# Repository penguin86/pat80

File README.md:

# Pat80

Pat80 Home Computer is an attempt to develop the simplest possible Zilog Z80 based computer in 2021.

## Hardware
Instead of being another single board computer, Pat80 focuses on modularity:
- The Core board contains Z80 CPU, 32k ram, 32k rom, memory and I/O decoding logic
- The Backplane is a stupid I/O bus board with no active components, 1 socket for the Core board and 8 sockets for I/O boards
- Each I/O board must implement tri-state and go to high impedance according to its EN pin to avoid bus contention
- The Power Supply module contains a 7805-based linear power supply capable of delivering 1A @5v for the core and I/O boards

Here is a picture of the early stages of development:

### I/O Boards

#### Parallel terminal interface
A parallel terminal based on Arduino is used for development purposes and will be replaced by an UART card.

#### Keyboard controller
Pat80 features a blue-switches mechanical matrix keyboard, seen by the system as a memory area in I/O space. The keyboard doesn't use interrupts and is polled by the OS.

#### Video controller
The monochrome 368x248 pixels video output is software-generated by an ATMega 1284 MCU. The timings are generated by the MCU's 16 bit internal timer and the vertical sync time is used to update the framebuffer.

## Software
The OS is a simple Memory Monitor. It can show memory content in hex and ascii with the typical hex editor tabular view.
Programs can be loaded from the keyboard, writing Z80 opcodes and data in hex. The program can be executed from any ram position and the Memory Monitor can be brought to screen in any moment issuing an INT signal (the Z80 INT pin should be connected to a button with pull-up resistor).
There is an experimental and unfinished quick load function using a python terminal to load a binary file directly to memory and execute it.

## Emulator
The pat80 memory monitor (the os) can be run in a z80 emulator. This repository contains an emulator as submodule, already set up to run the os.
To try it, head to `pat80-computer/software/z80-assembly/os/Makefile` and run `make run` to build the rom from assembly and start the emulator. You will see some windows showing the emulated computer's memory and register status and the pat80 memory monitor prompt.

## Status
The project is heavily work in progress.

### Working
- Core board
- Sound board
- Arduino parallel terminal with its own Python companion script (or any UART terminal)

The only fully working configuration as now is the Core board with two devices hooked to its I/O bus: the Arduino Parallel Terminal (see `pat80-io-devices/parallel-terminal` and `pat80-computer/software/z80-assembly/os/drivers/arduino_terminal.asm`) and the SN76489 sound chip (see `pat80-computer/software/z80-assembly/os/drivers/hd44780.asm`)

### Partially working
The keyboard is only partially tested, as it's not completed.

The composite video card is partially working, but has some nasty bugs on text cursor positioning and the graphics mode is not yet implemented (the only way to output graphics ATM is to place the bitmap in the MCU flash and load it to VRAM manually).

For the moment, better to stick with the Arduino Parallel Terminal.

### Not working
All the rest

## License
All the project is under GPL v3 license

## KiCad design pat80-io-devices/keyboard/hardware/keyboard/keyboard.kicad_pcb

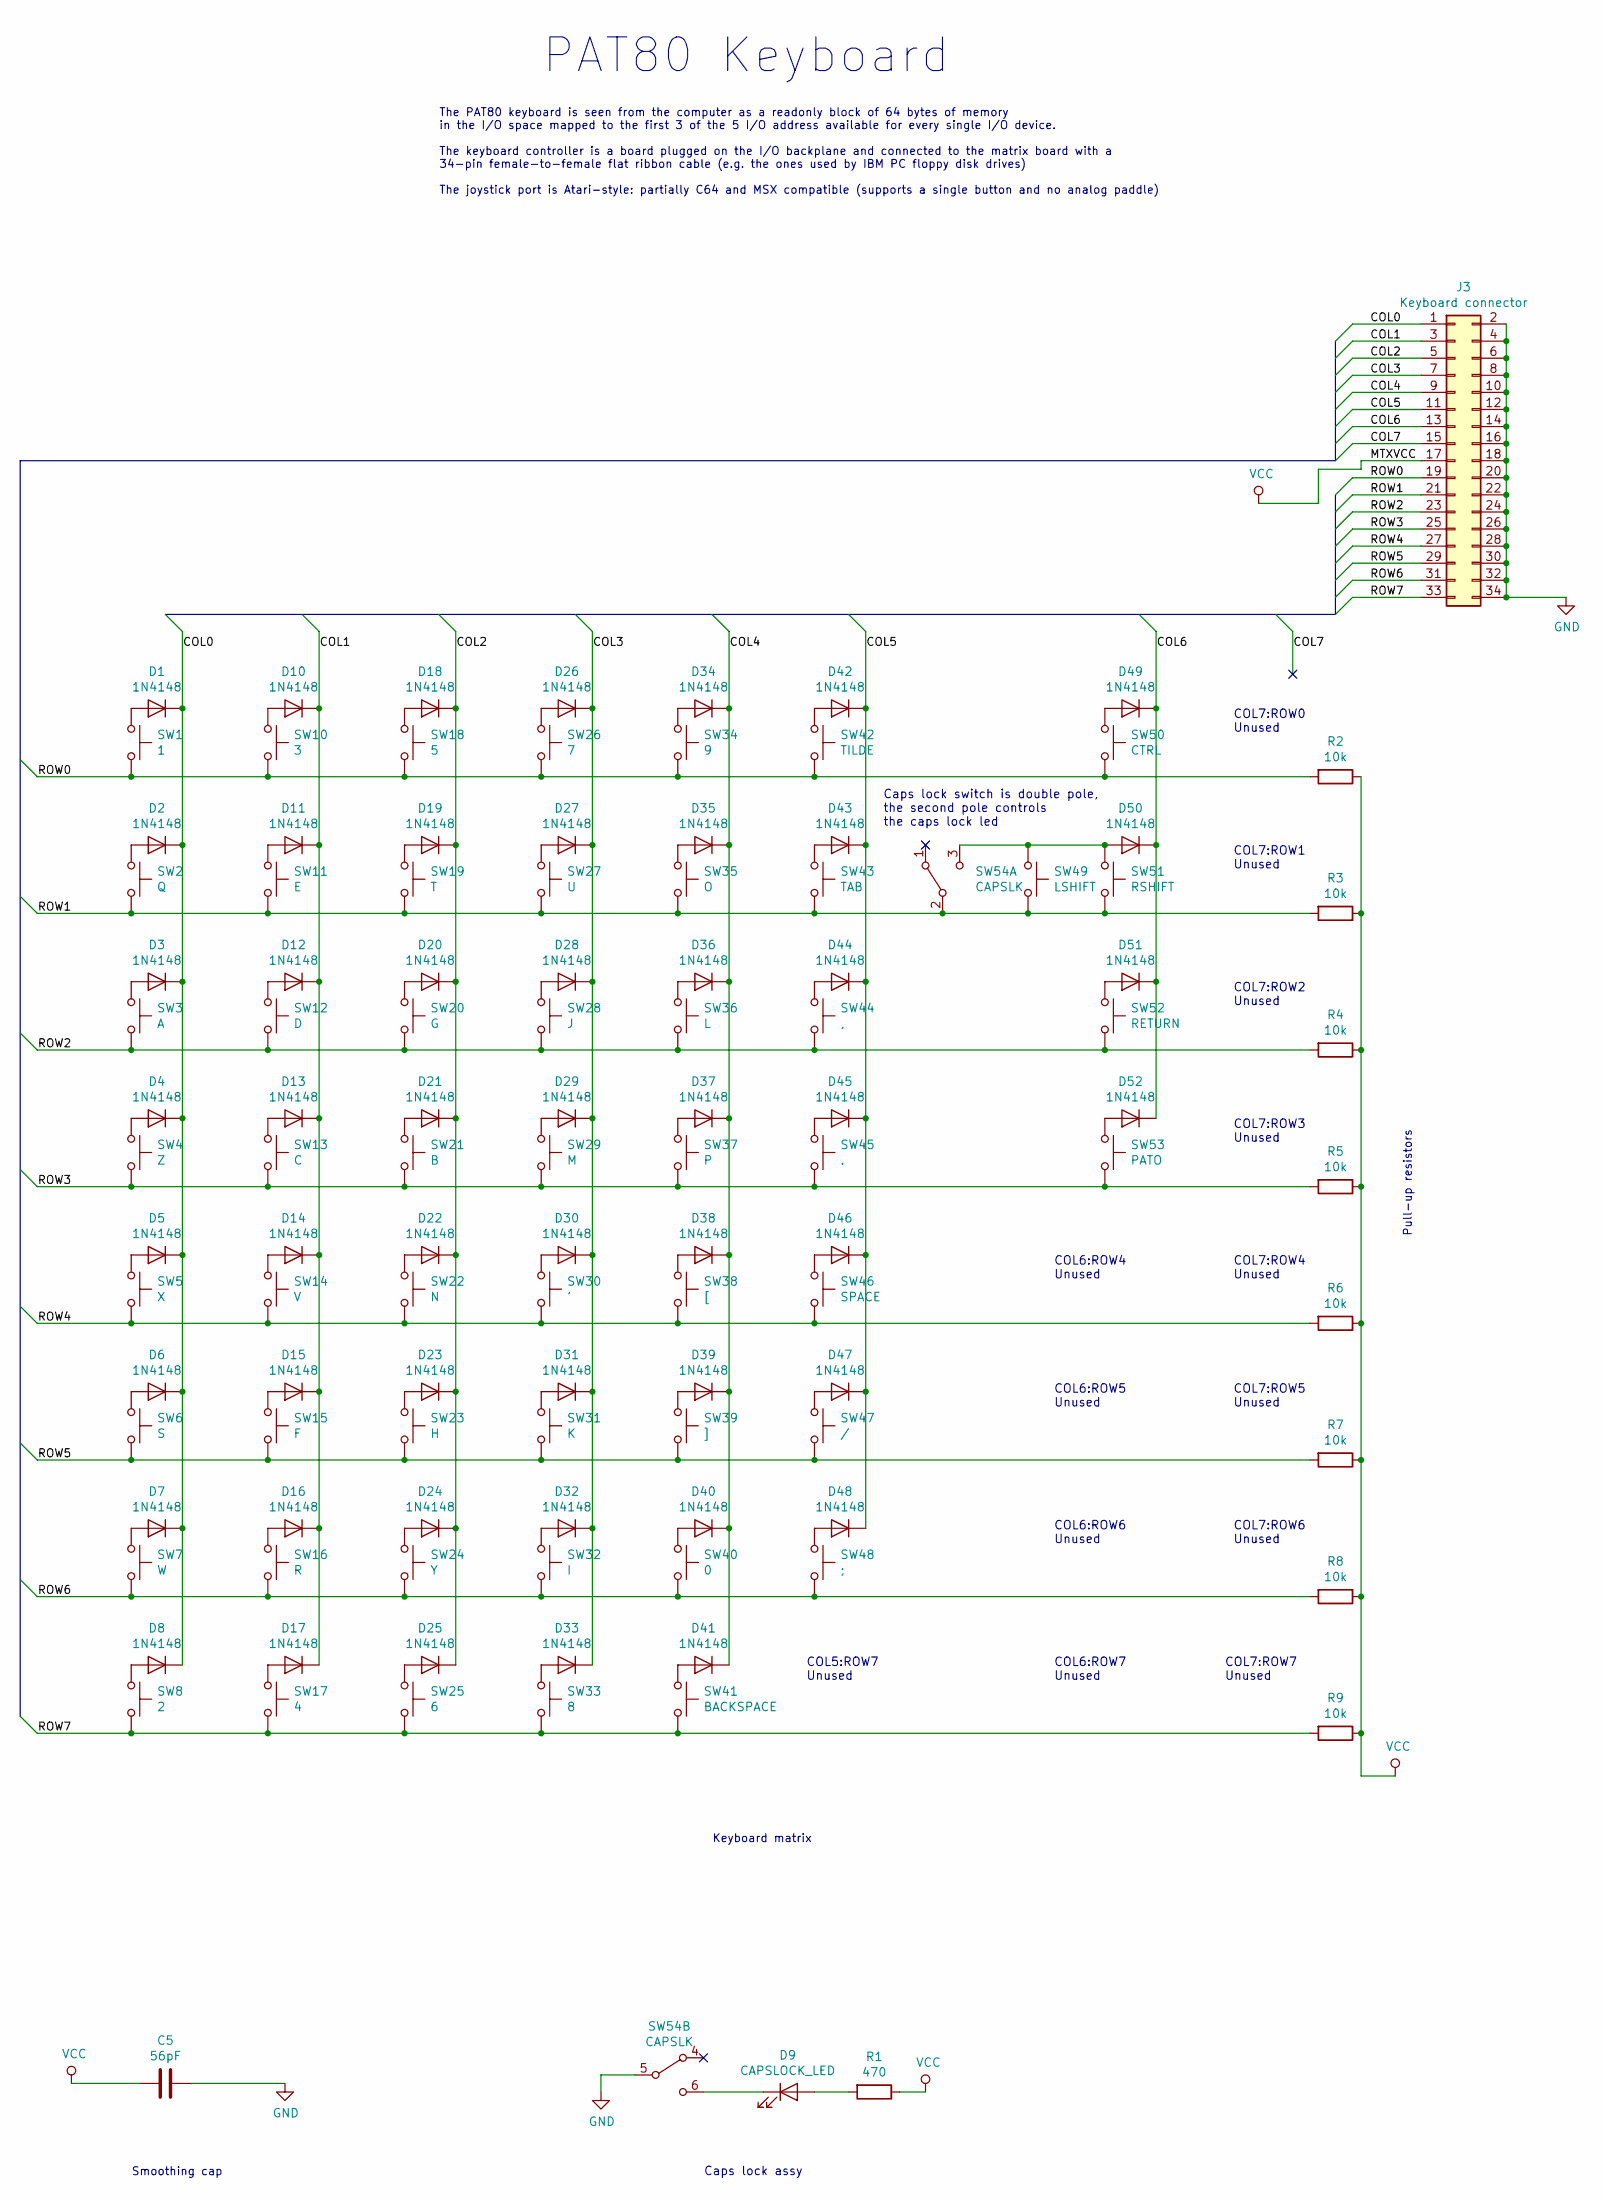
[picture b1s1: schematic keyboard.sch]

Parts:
C5: 56pF; CP_Radial_Tantal_D6.0mm_P5.00mm
D1, D2, D3, D4, D5, D6, D7, D8, D10, D11, D12, D13, D14, D15, D16, D17, D18, D19, D20, D21, D22, D23, D24, D25, D26, D27, D28, D29, D30, D31, D32, D33, D34, D35, D36, D37, D38, D39, D40, D41, D42, D43, D44, D45, D46, D47, D48, D49, D50, D51, D52: 1N4148; D_DO-41_SOD81_P7.62mm_Horizontal
D9: CAPSLOCK_LED; LED_D5.0mm
J3: Keyboard connector; PinHeader_2x17_P2.54mm_Vertical
R1: 470; R_Axial_DIN0207_L6.3mm_D2.5mm_P7.62mm_Horizontal
R2, R3, R4, R5, R6, R7, R8, R9: 10k; R_Axial_DIN0207_L6.3mm_D2.5mm_P7.62mm_Horizontal
SW1: 1; SW_Cherry_MX1A_1.00u_PCB
SW2: Q; SW_Cherry_MX1A_1.00u_PCB
SW3: A; SW_Cherry_MX1A_1.00u_PCB
SW4: Z; SW_Cherry_MX1A_1.00u_PCB
SW5: X; SW_Cherry_MX1A_1.00u_PCB
SW6: S; SW_Cherry_MX1A_1.00u_PCB
SW7: W; SW_Cherry_MX1A_1.00u_PCB
SW8: 2; SW_Cherry_MX1A_1.00u_PCB
SW10: 3; SW_Cherry_MX1A_1.00u_PCB
SW11: E; SW_Cherry_MX1A_1.00u_PCB
SW12: D; SW_Cherry_MX1A_1.00u_PCB
SW13: C; SW_Cherry_MX1A_1.00u_PCB
SW14: V; SW_Cherry_MX1A_1.00u_PCB
SW15: F; SW_Cherry_MX1A_1.00u_PCB
SW16: R; SW_Cherry_MX1A_1.00u_PCB
SW17: 4; SW_Cherry_MX1A_1.00u_PCB
SW18: 5; SW_Cherry_MX1A_1.00u_PCB
SW19: T; SW_Cherry_MX1A_1.00u_PCB
SW20: G; SW_Cherry_MX1A_1.00u_PCB
SW21: B; SW_Cherry_MX1A_1.00u_PCB
SW22: N; SW_Cherry_MX1A_1.00u_PCB
SW23: H; SW_Cherry_MX1A_1.00u_PCB
SW24: Y; SW_Cherry_MX1A_1.00u_PCB
SW25: 6; SW_Cherry_MX1A_1.00u_PCB
SW26: 7; SW_Cherry_MX1A_1.00u_PCB
SW27: U; SW_Cherry_MX1A_1.00u_PCB
SW28: J; SW_Cherry_MX1A_1.00u_PCB
SW29: M; SW_Cherry_MX1A_1.00u_PCB
SW30: '; SW_Cherry_MX1A_1.00u_PCB
SW31: K; SW_Cherry_MX1A_1.00u_PCB
SW32: I; SW_Cherry_MX1A_1.00u_PCB
SW33: 8; SW_Cherry_MX1A_1.00u_PCB
SW34: 9; SW_Cherry_MX1A_1.00u_PCB
SW35: O; SW_Cherry_MX1A_1.00u_PCB
SW36: L; SW_Cherry_MX1A_1.00u_PCB
SW37: P; SW_Cherry_MX1A_1.00u_PCB
SW38: [; SW_Cherry_MX1A_1.00u_PCB
SW39: ]; SW_Cherry_MX1A_1.00u_PCB
SW40: 0; SW_Cherry_MX1A_1.00u_PCB
SW41: BACKSPACE; SW_Cherry_MX1A_2.00u_Plate
SW42: TILDE; SW_Cherry_MX1A_1.00u_PCB
SW43: TAB; SW_Cherry_MX1A_1.50u_PCB
SW44: ,; SW_Cherry_MX1A_1.00u_PCB
SW45: .; SW_Cherry_MX1A_1.00u_PCB
SW46: SPACE; SW_Cherry_MX1A_2.25u_PCB
SW47: /; SW_Cherry_MX1A_1.00u_PCB
SW48: ;; SW_Cherry_MX1A_1.00u_PCB
SW49: LSHIFT; SW_Cherry_MX1A_1.25u_PCB
SW50: CTRL; SW_Cherry_MX1A_1.50u_PCB
SW51: RSHIFT; SW_Cherry_MX1A_1.75u_PCB
SW52: RETURN; SW_Cherry_MX1A_2.25u_PCB
SW53: PATO; SW_Cherry_MX1A_1.50u_PCB
SW54: CAPSLK; SW_TH_DPDT_Pushbutton_Latched

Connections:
/COL0: D1.1 (K), D2.1 (K), D3.1 (K), D4.1 (K), D5.1 (K), D6.1 (K), D7.1 (K), D8.1 (K), J3.1
/COL1: D10.1 (K), D11.1 (K), D12.1 (K), D13.1 (K), D14.1 (K), D15.1 (K), D16.1 (K), D17.1 (K), J3.3
/COL2: D18.1 (K), D19.1 (K), D20.1 (K), D21.1 (K), D22.1 (K), D23.1 (K), D24.1 (K), D25.1 (K), J3.5
/COL3: D26.1 (K), D27.1 (K), D28.1 (K), D29.1 (K), D30.1 (K), D31.1 (K), D32.1 (K), D33.1 (K), J3.7
/COL4: D34.1 (K), D35.1 (K), D36.1 (K), D37.1 (K), D38.1 (K), D39.1 (K), D40.1 (K), D41.1 (K), J3.9
/COL5: D42.1 (K), D43.1 (K), D44.1 (K), D45.1 (K), D46.1 (K), D47.1 (K), D48.1 (K), J3.11
/COL6: D49.1 (K), D50.1 (K), D51.1 (K), D52.1 (K), J3.13
/COL7: J3.15
/ROW0: J3.19, R2.2, SW1.2, SW10.2, SW18.2, SW26.2, SW34.2, SW42.2, SW50.2
/ROW1: J3.21, R3.2, SW2.2, SW11.2, SW19.2, SW27.2, SW35.2, SW43.2, SW49.2, SW51.2, SW54.2 (B)
/ROW2: J3.23, R4.2, SW3.2, SW12.2, SW20.2, SW28.2, SW36.2, SW44.2, SW52.2
/ROW3: J3.25, R5.2, SW4.2, SW13.2, SW21.2, SW29.2, SW37.2, SW45.2, SW53.2
/ROW4: J3.27, R6.2, SW5.2, SW14.2, SW22.2, SW30.2, SW38.2, SW46.2
/ROW5: J3.29, R7.2, SW6.2, SW15.2, SW23.2, SW31.2, SW39.2, SW47.2
/ROW6: J3.31, R8.2, SW7.2, SW16.2, SW24.2, SW32.2, SW40.2, SW48.2
/ROW7: J3.33, R9.2, SW8.2, SW17.2, SW25.2, SW33.2, SW41.2
GND: C5.1, J3.2, J3.4, J3.6, J3.8, J3.10, J3.12, J3.14, J3.16, J3.18, J3.20, J3.22, J3.24, J3.26, J3.28, J3.30, J3.32, J3.34, SW54.5 (B)
unnamed: D1.2 (A), SW1.1
unnamed: D2.2 (A), SW2.1
unnamed: D3.2 (A), SW3.1
unnamed: D4.2 (A), SW4.1
unnamed: D5.2 (A), SW5.1
unnamed: D6.2 (A), SW6.1
unnamed: D7.2 (A), SW7.1
unnamed: D8.2 (A), SW8.1
unnamed: D9.1 (K), SW54.6 (C)
unnamed: D9.2 (A), R1.2
unnamed: D10.2 (A), SW10.1
unnamed: D11.2 (A), SW11.1
unnamed: D12.2 (A), SW12.1
unnamed: D13.2 (A), SW13.1
unnamed: D14.2 (A), SW14.1
unnamed: D15.2 (A), SW15.1
unnamed: D16.2 (A), SW16.1
unnamed: D17.2 (A), SW17.1
unnamed: D18.2 (A), SW18.1
unnamed: D19.2 (A), SW19.1
unnamed: D20.2 (A), SW20.1
unnamed: D21.2 (A), SW21.1
unnamed: D22.2 (A), SW22.1
unnamed: D23.2 (A), SW23.1
unnamed: D24.2 (A), SW24.1
unnamed: D25.2 (A), SW25.1
unnamed: D26.2 (A), SW26.1
unnamed: D27.2 (A), SW27.1
unnamed: D28.2 (A), SW28.1
unnamed: D29.2 (A), SW29.1
unnamed: D30.2 (A), SW30.1
unnamed: D31.2 (A), SW31.1
unnamed: D32.2 (A), SW32.1
unnamed: D33.2 (A), SW33.1
unnamed: D34.2 (A), SW34.1
unnamed: D35.2 (A), SW35.1
unnamed: D36.2 (A), SW36.1
unnamed: D37.2 (A), SW37.1
unnamed: D38.2 (A), SW38.1
unnamed: D39.2 (A), SW39.1
unnamed: D40.2 (A), SW40.1
unnamed: D41.2 (A), SW41.1
unnamed: D42.2 (A), SW42.1
unnamed: D43.2 (A), SW43.1
unnamed: D44.2 (A), SW44.1
unnamed: D45.2 (A), SW45.1
unnamed: D46.2 (A), SW46.1
unnamed: D47.2 (A), SW47.1
unnamed: D48.2 (A), SW48.1
unnamed: D49.2 (A), SW50.1
unnamed: D50.2 (A), SW49.1, SW51.1, SW54.3 (C)
unnamed: D51.2 (A), SW52.1
unnamed: D52.2 (A), SW53.1
VCC: C5.2, J3.17, R1.1, R2.1, R3.1, R4.1, R5.1, R6.1, R7.1, R8.1, R9.1

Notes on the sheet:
PAT80 Keyboard
The PAT80 keyboard is seen from the computer as a readonly block of 64 bytes of memory in the I/O space mapped to the first 3 of the 5 I/O address available for every single I/O device. The keyboard controller is a board plugged on the I/O backplane and connected to the matrix board with a 34-pin f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
Smoothing cap
COL7:ROW1 Unused
COL7:ROW0 Unused
Keyboard matrix
COL7:ROW7 Unused
COL7:ROW6 Unused
COL7:ROW5 Unused
COL7:ROW2 Unused
COL7:ROW3 Unused
COL7:ROW4 Unused
COL6:ROW7 Unused
COL6:ROW6 Unused
COL6:ROW5 Unused
COL6:ROW4 Unused
COL5:ROW7 Unused
Pull-up resistors
Caps lock assy
Caps lock switch is double pole, the second pole controls the caps lock led

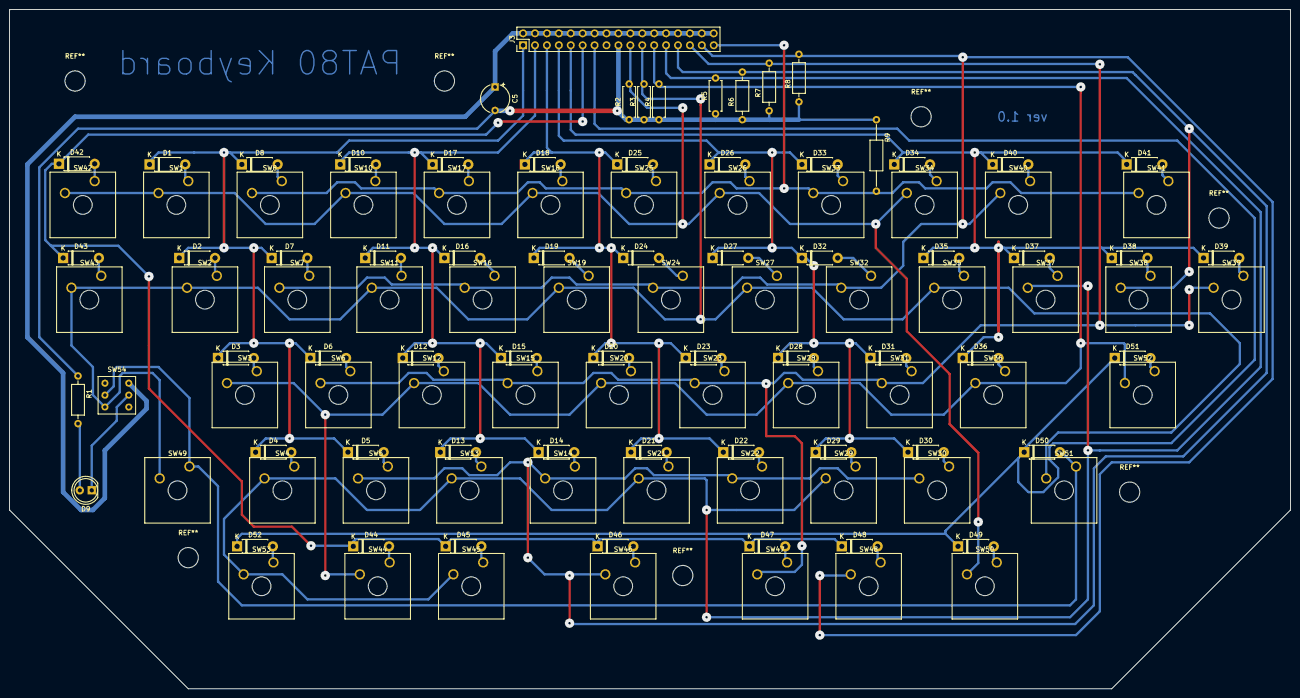
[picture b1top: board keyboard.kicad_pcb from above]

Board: 2 copper layers, 273.1 x 144.8 mm, 116 parts (0 on the bottom side), 70 nets.

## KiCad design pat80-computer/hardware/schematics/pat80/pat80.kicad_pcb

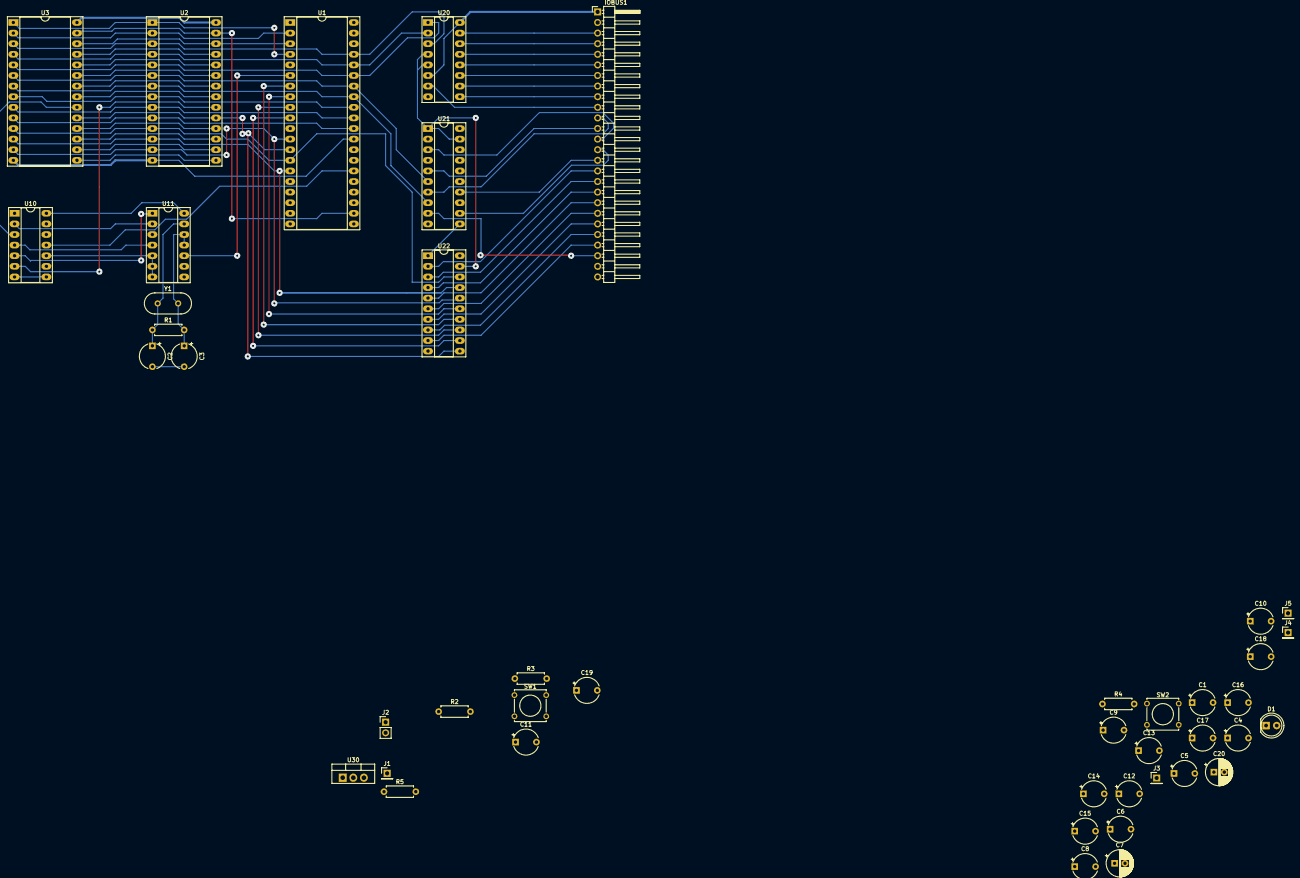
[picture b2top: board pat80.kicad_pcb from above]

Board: 2 copper layers, 44 parts (0 on the bottom side), 65 nets.

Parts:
C1, C6: 10uF; CP_Radial_Tantal_D6.0mm_P5.00mm
C2, C3: 30pF; CP_Radial_Tantal_D6.0mm_P5.00mm
C4: 0,22uF; CP_Radial_Tantal_D6.0mm_P5.00mm
C5: 0,1uF; CP_Radial_Tantal_D6.0mm_P5.00mm
C7, C20: 470uF; CP_Radial_D6.3mm_P2.50mm
C8, C11, C13, C14, C16, C18: 100nF; CP_Radial_Tantal_D6.0mm_P5.00mm
C9, C10, C12, C15, C17, C19: 56pF; CP_Radial_Tantal_D6.0mm_P5.00mm
D1: LED; LED_D5.0mm
IOBUS1: IO_bus_conn; PinHeader_1x26_P2.54mm_Horizontal
J1: panel_btn_brk; PinHeader_1x01_P2.54mm_Vertical
J2: Power input; PinHeader_1x02_P2.54mm_Vertical
J3: panel_led_halt; PinHeader_1x01_P2.54mm_Vertical
J4: panel_btn_rst; PinHeader_1x01_P2.54mm_Vertical
J5: nmi; PinHeader_1x01_P2.54mm_Vertical
R1: 3,3M; R_Axial_DIN0207_L6.3mm_D2.5mm_P7.62mm_Horizontal
R2, R3: 10k; R_Axial_DIN0207_L6.3mm_D2.5mm_P7.62mm_Horizontal
R4: 470; R_Axial_DIN0207_L6.3mm_D2.5mm_P7.62mm_Horizontal
R5: 270k; R_Axial_DIN0207_L6.3mm_D2.5mm_P7.62mm_Horizontal
SW1: SW_Push; SW_Tactile_Straight_KSA0Axx1LFTR
SW2: Break; SW_Tactile_Straight_KSA0Axx1LFTR
U1: Z80CPU; DIP-40_W15.24mm_Socket_LongPads
U2: 256k (32k x 8) EEPROM; DIP-28_W15.24mm_Socket_LongPads
U3: 256k (32k x 8) SRAM; DIP-28_W15.24mm_Socket_LongPads
U10: 74HC32; DIP-14_W7.62mm_Socket_LongPads
U11: 74HC04; DIP-14_W7.62mm_Socket_LongPads
U20: 74HC138; DIP-16_W7.62mm_Socket_LongPads
U21: 74HC244; DIP-20_W7.62mm_Socket_LongPads
U22: 74HC245; DIP-20_W7.62mm_Socket_LongPads
U30: LM7805_TO220; TO-220-3_Vertical
Y1: 4Mhz; Crystal_HC18-U_Vertical

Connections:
/A0: U1.30, U2.10, U3.10, U21.17
/A1: U1.31, U2.9, U3.9, U21.15
/A2: U1.32, U2.8, U3.8, U21.13
/A3: U1.33, U2.7, U3.7, U21.8
/A4: U1.34, U2.6, U3.6, U21.6
/A5: U1.35, U2.5, U3.5, U20.1
/A6: U1.36, U2.4, U3.4, U20.2
/A7: U1.37, U2.3, U3.3, U20.3
/A8: U1.38, U2.25, U3.25
/A9: U1.39, U2.24, U3.24
/A10: U1.40, U2.21, U3.21
/A11: U1.1, U2.23, U3.23
/A12: U1.2, U2.2, U3.2
/A13: U1.3, U2.26, U3.26
/A14: U1.4, U2.1, U3.1
/A15: U1.5, U10.5, U11.1
/D0: U1.14, U2.11, U3.11, U22.18
/D1: U1.15, U2.12, U3.12, U22.17
/D2: U1.12, U2.13, U3.13, U22.16
/D3: U1.8, U2.15, U3.15, U22.15
/D4: U1.7, U2.16, U3.16, U22.14
/D5: U1.9, U2.17, U3.17, U22.13
/D6: U1.10, U2.18, U3.18, U22.12
/D7: U1.13, U2.19, U3.19, U22.11
/IOADDR0: IOBUS1.11, U21.7
/IOADDR1: IOBUS1.12, U21.5
/IOADDR2: IOBUS1.13, U21.3
/IOADDR3: IOBUS1.14, U21.12
/IOADDR4: IOBUS1.15, U21.14
/IOD0: IOBUS1.16, U22.2
/IOD1: IOBUS1.17, U22.3
/IOD2: IOBUS1.18, U22.4
/IOD3: IOBUS1.19, U22.5
/IOD4: IOBUS1.20, U22.6
/IOD5: IOBUS1.21, U22.7
/IOD6: IOBUS1.22, U22.8
/IOD7: IOBUS1.23, U22.9
/IOEN0: IOBUS1.3, U20.15
/IOEN1: IOBUS1.4, U20.14
/IOEN2: IOBUS1.5, U20.13
/IOEN3: IOBUS1.6, U20.12
/IOEN4: IOBUS1.7, U20.11
/IOEN5: IOBUS1.8, U20.10
/IOEN6: IOBUS1.9, U20.9
/IOEN7: IOBUS1.10, U20.7
/IORQ: U1.20, U20.4, U20.5, U21.1, U21.19, U22.19
/IOWR: IOBUS1.24, U21.9
/RAMEN: U3.20, U10.3
/RD: U1.21, U2.22, U3.22
/ROMEN: U2.20, U10.6
/WR: U1.22, U2.27, U3.27, U21.11, U22.1
GND: C1.2, C2.2, C3.2, C4.2, C5.2, C6.2, C7.2, C8.1, C9.1, C10.1, C11.1, C12.1, C13.1, C14.1, C15.1, C16.1, C17.1, C18.1, C19.1, C20.2, IOBUS1.2, IOBUS1.25, J2.2, SW1.1, SW2.1, U1.29, U2.14, U3.14, U20.8, U21.10, U22.10, U30.2
unnamed: C1.1, J1.1, R2.1, SW2.2, U1.16
unnamed: C2.1, R1.1, U11.13, Y1.1
unnamed: C3.1, R1.2, U11.11, U11.12, Y1.2
unnamed: C4.1, J2.1, U30.1
unnamed: C6.1, J4.1, R5.2, SW1.2, U10.12, U10.13
unnamed: D1.1, J3.1, U1.18
unnamed: D1.2, R4.1
unnamed: R3.1, U1.17
unnamed: U1.6, U11.10
unnamed: U1.26, U10.11
unnamed: U10.1, U10.4, U11.4
unnamed: U10.2, U11.2
VCC: C5.1, C7.1, C8.2, C9.2, C10.2, C11.2, C12.2, C13.2, C14.2, C15.2, C16.2, C17.2, C18.2, C19.2, C20.1, IOBUS1.1, IOBUS1.26, R2.2, R3.2, R4.2, R5.1, U1.11, U1.24, U1.25, U2.28, U3.28, U20.6, U20.16, U21.20, U22.20, U30.3

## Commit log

2020-10-14 Working debugger, non-working programmer and lcd test procedure with lcd mapped in memory
2020-10-18 hd44780 display debugger
2020-10-24 Working LCD!
2020-10-26 WIP BIOS
2020-10-27 readme
2020-10-27 Split bios in multiple asm files
2020-10-27 Experimenting with lcd cursor location instructions
2020-11-01 Added IO address decoding. Lorem ipsum demo (without sorting LCD cursor addressing problems).
2020-11-01 WIP keyboard driver
2020-11-01 Quick 2x2 keyboard test
2020-11-07 Decoding logic with bottom 32k to rom, upper 32k to ram and 8 I/O ports with 32 addresses each
2020-11-19 WIP Arduino VGA adapter
2020-11-19 Untested char output for VGA adapter
2020-11-21 Testing AV out: timing issues
2020-11-22 Working echo test for arduino terminal
2020-11-22 Added Arduino terminal, moved drivers config variables to each driver asm file
2020-11-23 Implemented read char and readline in arduino terminal driver
2020-11-23 WIP: Monitor asm file stub
2020-11-24 Code refactoring, working char read and print, working line print, not working line read
2020-11-25 WIP Monitor
2020-11-25 First working interactive shell for memory monitor
2020-11-25 Working hex parsing in monitor
2020-11-25 WIP Immediate function in monitor (reads bytes from stdin and executes immediately)
2020-11-29 Trying optimizing terminal to stay under 600nS per clock cycle (not working ATM)
2020-11-29 Maybe found bug in arduino terminal
2020-12-02 Wip writing SN76489 test sketch
2020-12-02 SN76489 sound test with Arduino
2020-12-05 Updated makefile to show rom size!
2020-12-05 Sound working at very low cpu frequencies
2020-12-06 NS76489 digital pin order is fucking inverted! D0 is the MSB, D7 the LSB.
2020-12-06 Refactored ASM, added sound support
2020-12-06 Spaces
2020-12-09 Code clean
2020-12-09 Seemingly working immediate load in monitor
2020-12-09 WIP Writing terminal deployer
2020-12-10 WIP Writing terminal emulator
2020-12-10 WIP python terminal emulator
2020-12-11 Working terminal read
2020-12-11 Fixed line feed
2020-12-11 WIP reading from terminal
2020-12-12 Implemented ADB in terminal_emulator
2020-12-13 Pat80 logo
2020-12-13 Media assets and first post
2020-12-13 Working data transmission in python terminal
2020-12-15 Python terminal emu not working with Python versions less than 3
2020-12-15 Trying to get Immediate to work
2020-12-15 Terminal emu: restoring cursor position after ADB
2020-12-16 WIP reimplementing serial terminal with DATA_AVAILABLE register
2020-12-16 Working DUMP stub in monitor
2020-12-17 Dump function in monitor
2020-12-17 Working DUMP in Monitor
2020-12-17 Line numbers
2020-12-18 Working SET in Monitor (one bit at time, for now)
2020-12-21 RUN accepts an argument
2020-12-21 Monitor DUMP prints bytes with the standard hex editor layout
2020-12-26 Completed SET command
2020-12-26 WIP Zero command in monitor
2020-12-26 Hello world program to be used for monitor demo
2020-12-26 Testing sdcard initialization with Arduino
2020-12-29 Trying to obtain fixed position system calls. Not working ATM
2020-12-30 First os version with ABI number and working system calls
2020-12-30 Moved "bios" to "os"
2020-12-30 WIP Monitor ADB function with heading bytes defining stream length
2021-01-01 Uncommitted changes
2021-01-01 Working ADB transfer at very low speeds (adding a delay in python terminal)
2021-01-02 WIP immediate return to monitor via interrupt
2021-01-02 Reorganized folders, added pal-adapter io device folder
2021-01-02 pal-adapter: fuses config and readme
2021-01-02 Horyzontal timings (working, checked with oscilloscope)
2021-01-02 First working image with a lot of jitter
2021-01-03 Interrupt brings up Monitor: working, but calling "run" leaves garbage in the SP
2021-01-03 New test pattern, still hsync issues
2021-01-03 Fixed timings
2021-01-05 Loses sync when loading from memory
2021-01-07 WIP fucking video generation
2021-01-07 Read framebuffer from mc's memory
2021-01-07 Fixed memory hsync
2021-01-08 Scrambled image due to inverted bit order in every of the 52 line byte chunks
2021-01-08 Polish
2021-01-08 Working stable non-interlaced image of cat read from rom into ram framebuffer
2021-01-09 Documented idea of interrupt-driven video generation
2021-01-10 WIP documenting interfacing idea
2021-01-10 Not working implementation of timer-driven video signal generation
2021-01-10 Not working implementation of timer-driven video signal generation 2
2021-01-13 Using official mc device definition
2021-01-16 Working timer1, but wrong timings
2021-01-17 Working on timings
2021-01-17 Fixed halved number of sync pulses
2021-01-17 Temporary fix for first short sync timer after image firing in advance
2021-01-19 Renamed r0 to A
2021-01-19 Refactoring
2021-01-19 Copying data bus to framebuffer memory, but ignoring clock signal
2021-01-22 Started working on characters
2021-01-24 Big refactoring and first character generator implementation
2021-01-24 Testing char drawing routine
2021-01-24 Testing character generation
2021-01-25 Working character output, non working return to home
2021-01-26 Single line chars demo
2021-01-26 First working text mode without end of screen scroll
2021-01-27 Back working on communication
2021-02-03 Started implementing PS/2 Keyboard driver
2021-02-03 WIP PS/2 keyboard driver
2021-02-07 Reading ps/2 keyboard, but somehow, keycodes are decremented by 1
2021-02-09 WIP PS/2 Keyboard
2021-02-12 ps/2 debugger
2021-02-12 Characters test prior to memory map refactor
2021-02-12 Reduced columns to 46
2021-02-12 horyzontally centered image in CRT
2021-02-12 Trying to fit vertically the image. Heavily distorted on CRT.
2021-02-14 Perfected timings
2021-02-14 Extended image to 368x256
2021-02-15 Working EOL
2021-02-15 WIP newline and end-of-screen shift
2021-02-16 Minor fix
2021-02-20 Refinements
2021-02-20 Testing with cat image
2021-02-20 Straight, but unstable image. Some unwanted spaces during vertical sync
2021-02-20 Fixed cat size to new resolution
2021-02-22 Untested code
2021-02-22 Working end of screen scrolling
2021-02-22 Working carriage return
2021-02-25 Bugfix, refactoring
2021-02-28 Reduced problem on char draw
2021-03-01 WIP memory check in memory monitor
2021-03-01 Working on memtest
2021-03-05 WIP UART Rx simulation with Logisim
2021-03-06 Working UART simulation without rx clock sync
2021-03-06 UART: Thinking how to delay sampling to mid clock
2021-03-15 WIP UART sampling at mid clock
2021-03-15 WIP Mainboard schematics: added CPU, RAM, ROM, Addr and data bus.
    TODO: Fix external dependency
2021-03-15 Removed symbol using third party library
2021-03-15 Reset circuit
2021-03-17 WIP Schematics
2021-03-19 Memory decoding, WIP IO decoding
2021-03-20 Almost finished transcribing mainboard schematics
2021-03-20 Schematic complete, commit before assigning footprints
2021-03-20 Schematics: assigned footprints, created ratsnest
2021-03-21 Connector description
2021-03-21 WIP Keyboard schematics (too much keys)
2021-03-22 WIP Keyboard schematics
2021-03-24 WIP routing mainboard
2021-03-26 WIP mainboard routing
2021-03-26 Completed keyboard schematics
2021-03-27 Final keyboard schematics with joystick port
2021-03-27 Assigning footprints
2021-03-27 Split keyboard into two different schematics: kb controller and kb assembly. Started routing keyboard pcb.
2021-03-27 Uncommitted files
2021-03-27 Fine-positioned caps lock switch
2021-03-27 Distanced keys to avoid interference
2021-03-28 WIP routing keyboard
2021-03-30 Completed routing keyboard PCB
2021-03-30 Keyboard PCB: edge cuts and mounting holes
2021-04-02 Fixed caps lock footprint error
2021-04-02 Refinement
2021-07-11 Ready for github publishing
2021-07-11 Fixed image spacing in readme
2021-07-11 Missing image
2022-02-06 Setting up PAT80 Emulator
2023-12-02 Added emulator as submodule, updated makefile to run directly os in emulator
